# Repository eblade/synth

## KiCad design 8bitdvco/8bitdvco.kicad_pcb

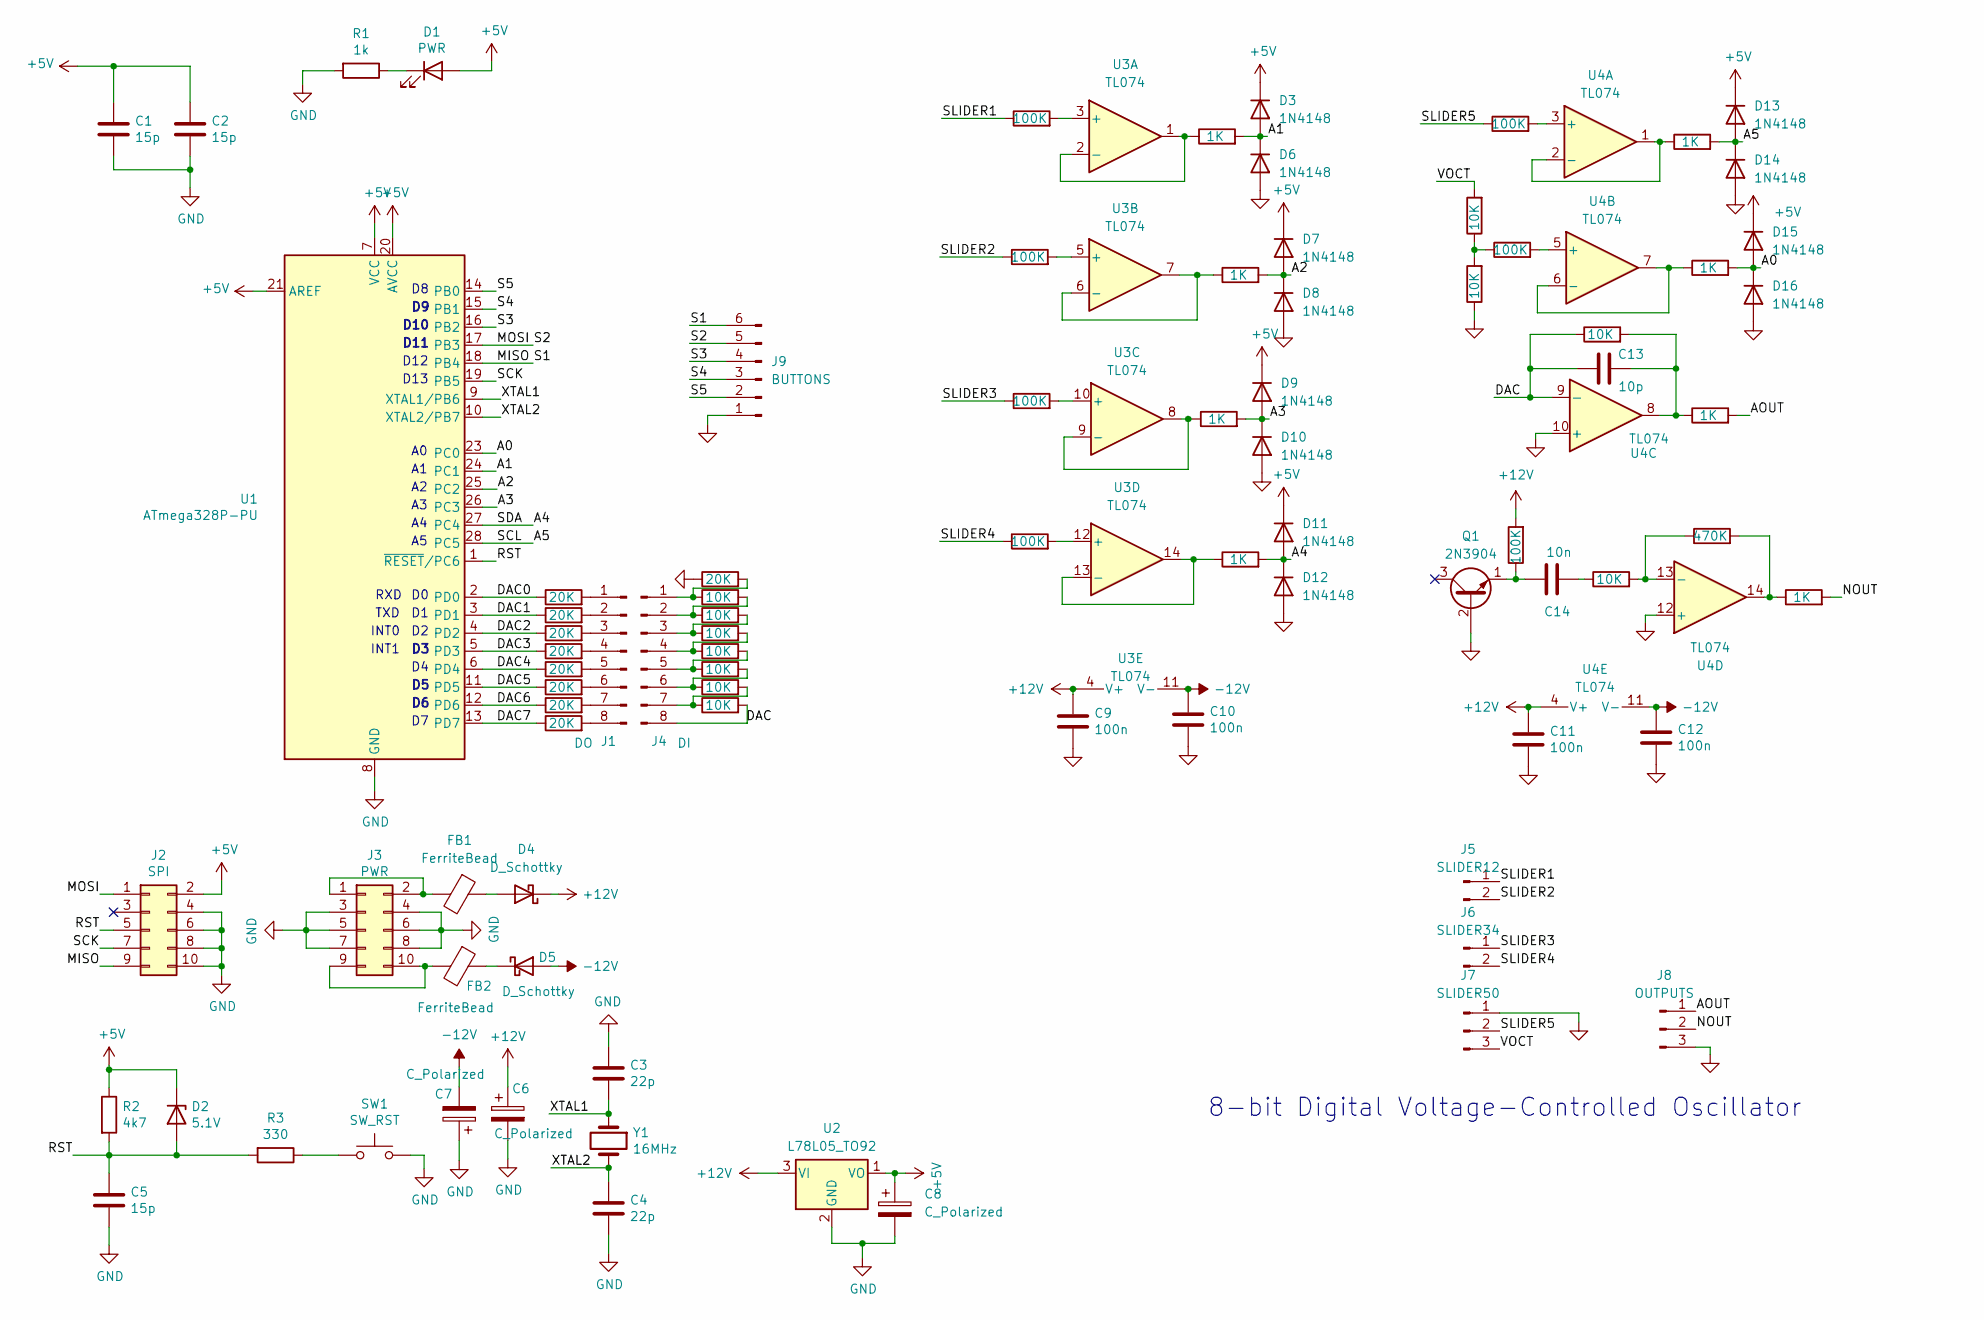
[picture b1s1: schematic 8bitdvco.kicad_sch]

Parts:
C1, C2, C5: 15p; C_Disc_D3.0mm_W1.6mm_P2.50mm
C3, C4: 22p; C_Disc_D3.0mm_W1.6mm_P2.50mm
C6, C7, C8: C_Polarized; CP_Radial_D8.0mm_P2.50mm
C9, C10, C11, C12: 100n; C_Disc_D3.0mm_W1.6mm_P2.50mm
C13: 10p; C_Disc_D3.0mm_W1.6mm_P2.50mm
C14: 10n; C_Disc_D3.0mm_W1.6mm_P2.50mm
D1: PWR; LED_D3.0mm
D2: 5.1V; D_A-405_P7.62mm_Horizontal
D3, D6, D7, D8, D9, D10, D11, D12, D13, D14, D15, D16: 1N4148; D_DO-35_SOD27_P7.62mm_Horizontal
D4, D5: D_Schottky; D_DO-35_SOD27_P7.62mm_Horizontal
FB1, FB2: FerriteBead; R_Axial_DIN0309_L9.0mm_D3.2mm_P12.70mm_Horizontal
J1: DO; PinHeader_1x08_P2.54mm_Vertical
J2: SPI; PinHeader_2x05_P2.54mm_Vertical
J3: PWR; PinHeader_2x05_P2.54mm_Vertical
J4: DI; PinHeader_1x08_P2.54mm_Vertical
J5: SLIDER12; PinHeader_1x02_P2.54mm_Vertical
J6: SLIDER34; PinHeader_1x02_P2.54mm_Vertical
J7: SLIDER50; PinHeader_1x03_P2.54mm_Vertical
J8: OUTPUTS; PinHeader_1x03_P2.54mm_Vertical
J9: BUTTONS; PinHeader_1x06_P2.54mm_Vertical
Q1: 2N3904; TO-92_Inline
R1: 1k; R_Axial_DIN0204_L3.6mm_D1.6mm_P7.62mm_Horizontal
R2: 4k7; R_Axial_DIN0204_L3.6mm_D1.6mm_P7.62mm_Horizontal
R3: 330; R_Axial_DIN0204_L3.6mm_D1.6mm_P7.62mm_Horizontal
R4, R5, R6, R7, R8, R9, R10, R32, R33, R34, R38: 10K; R_Axial_DIN0204_L3.6mm_D1.6mm_P7.62mm_Horizontal
R11, R14, R15, R16, R17, R18, R19, R20, R21: 20K; R_Axial_DIN0204_L3.6mm_D1.6mm_P7.62mm_Horizontal
R12, R23, R24, R25, R28, R29, R35, R36: 1K; R_Axial_DIN0204_L3.6mm_D1.6mm_P7.62mm_Horizontal
R13, R22, R26, R27, R30, R31, R39: 100K; R_Axial_DIN0204_L3.6mm_D1.6mm_P7.62mm_Horizontal
R37: 470K; R_Axial_DIN0204_L3.6mm_D1.6mm_P7.62mm_Horizontal
SW1: SW_RST; SW_PUSH_6mm_H4.3mm
U1: ATmega328P-PU; DIP-28_W7.62mm
U2: L78L05_TO92; TO-92_Inline
U3, U4: TL074; DIP-14_W7.62mm_LongPads
Y1: 16MHz; Crystal_HC18-U_Vertical

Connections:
+5V: C1.2, C2.2, C8.1, D1.2 (A), D2.1 (K), D3.1 (K), D7.1 (K), D9.1 (K), D11.1 (K), D13.1 (K), D15.1 (K), J2.2, R2.1, U1.7 (VCC), U1.20 (AVCC), U1.21 (AREF), U2.1 (VO)
+12V: C6.1, C9.2, C11.2, D4.1 (K), R39.2, U2.3 (VI), U3.4 (V+), U4.4 (V+)
-12V: C7.2, C10.2, C12.2, D5.2 (A), U3.11 (V-), U4.11 (V-)
/A0: D15.2 (A), D16.1 (K), R29.2, U1.23 (PC0)
/A1: D3.2 (A), D6.1 (K), R12.2, U1.24 (PC1)
/A2: D7.2 (A), D8.1 (K), R23.2, U1.25 (PC2)
/A3: D9.2 (A), D10.1 (K), R24.2, U1.26 (PC3)
/A4: D11.2 (A), D12.1 (K), R25.2, U1.27 (PC4)
/A5: D13.2 (A), D14.1 (K), R28.2, U1.28 (PC5)
/AOUT: J8.1, R35.2
/DAC: C13.1, J4.8, R10.2, R34.1, U4.9 (-)
/DAC0: R14.1, U1.2 (PD0)
/DAC1: R15.1, U1.3 (PD1)
/DAC2: R16.1, U1.4 (PD2)
/DAC3: R17.1, U1.5 (PD3)
/DAC4: R18.1, U1.6 (PD4)
/DAC5: R19.1, U1.11 (PD5)
/DAC6: R20.1, U1.12 (PD6)
/DAC7: R21.1, U1.13 (PD7)
/MISO: J2.9, J9.6, U1.18 (PB4)
/MOSI: J2.1, J9.5, U1.17 (PB3)
/NOUT: J8.2, R36.2
/RST: C5.2, D2.2 (A), J2.5, R2.2, R3.2, U1.1 (~RESET/PC6)
/S3: J9.4, U1.16 (PB2)
/S4: J9.3, U1.15 (PB1)
/S5: J9.2, U1.14 (PB0)
/SCK: J2.7, U1.19 (PB5)
/SLIDER1: J5.1, R13.1
/SLIDER2: J5.2, R22.1
/SLIDER3: J6.1, R26.1
/SLIDER4: J6.2, R27.1
/SLIDER5: J7.2, R30.1
/VOCT: J7.3, R32.2
/XTAL1: C3.2, U1.9 (XTAL1/PB6), Y1.1
/XTAL2: C4.1, U1.10 (XTAL2/PB7), Y1.2
GND: C1.1, C2.1, C3.1, C4.2, C5.1, C6.2, C7.1, C8.2, C9.1, C10.1, C11.1, C12.1, D6.2 (A), D8.2 (A), D10.2 (A), D12.2 (A), D14.2 (A), D16.2 (A), J2.4, J2.6, J2.8, J2.10, J3.3, J3.4, J3.5, J3.6, J3.7, J3.8, J7.1, J8.3, J9.1, Q1.2 (B), R1.2, R11.1, R33.1, SW1.2, U1.8 (GND), U1.22 (GND), U2.2 (GND), U4.10 (+), U4.12 (+)
unnamed: C13.2, R34.2, R35.1, U4.8
unnamed: C14.1, R38.1
unnamed: D1.1 (K), R1.1
unnamed: D4.2 (A), FB1.1
unnamed: D5.1 (K), FB2.1
unnamed: J1.1, R14.2
unnamed: J1.2, R15.2
unnamed: J1.3, R16.2
unnamed: J1.4, R17.2
unnamed: J1.5, R18.2
unnamed: J1.6, R19.2
unnamed: J1.7, R20.2
unnamed: J1.8, R21.2
unnamed: FB1.2, J3.1, J3.2
unnamed: FB2.2, J3.9, J3.10
unnamed: J4.1, R4.1, R11.2
unnamed: J4.2, R4.2, R5.1
unnamed: J4.3, R5.2, R6.1
unnamed: J4.4, R6.2, R7.1
unnamed: J4.5, R7.2, R8.1
unnamed: J4.6, R8.2, R9.1
unnamed: J4.7, R9.2, R10.1
unnamed: C14.2, Q1.1 (E), R39.1
unnamed: R3.1, SW1.1
unnamed: R31.1, R32.1, R33.2
unnamed: R36.1, R37.2, U4.14
unnamed: R13.2, U3.3 (+)
unnamed: R12.1, U3.1, U3.2 (-)
unnamed: R22.2, U3.5 (+)
unnamed: R23.1, U3.6 (-), U3.7
unnamed: R26.2, U3.10 (+)
unnamed: R24.1, U3.8, U3.9 (-)
unnamed: R27.2, U3.12 (+)
unnamed: R25.1, U3.13 (-), U3.14
unnamed: R30.2, U4.3 (+)
unnamed: R28.1, U4.1, U4.2 (-)
unnamed: R31.2, U4.5 (+)
unnamed: R29.1, U4.6 (-), U4.7
unnamed: R37.1, R38.2, U4.13 (-)

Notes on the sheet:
D12
D10
RXD
D13
D11
INT1
TXD
8-bit Digital Voltage-Controlled Oscillator
INT0

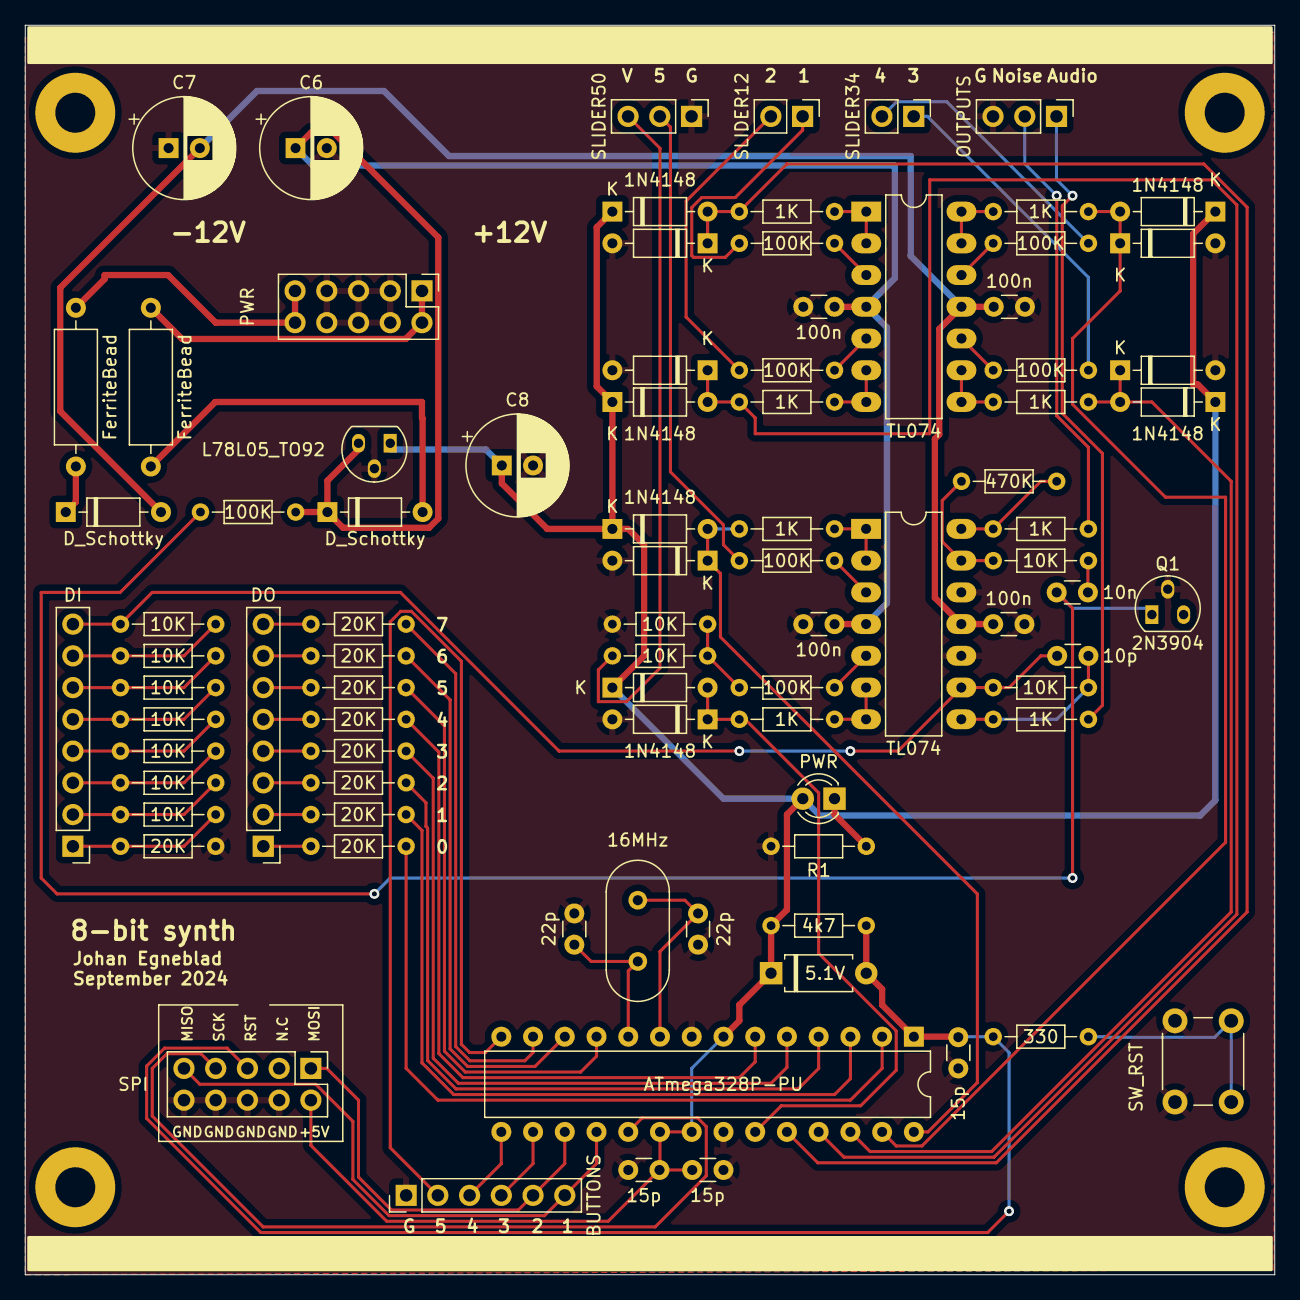
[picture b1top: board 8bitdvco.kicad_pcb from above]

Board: 2 copper layers, 100.0 x 100.0 mm, 87 parts (0 on the bottom side), 75 nets.

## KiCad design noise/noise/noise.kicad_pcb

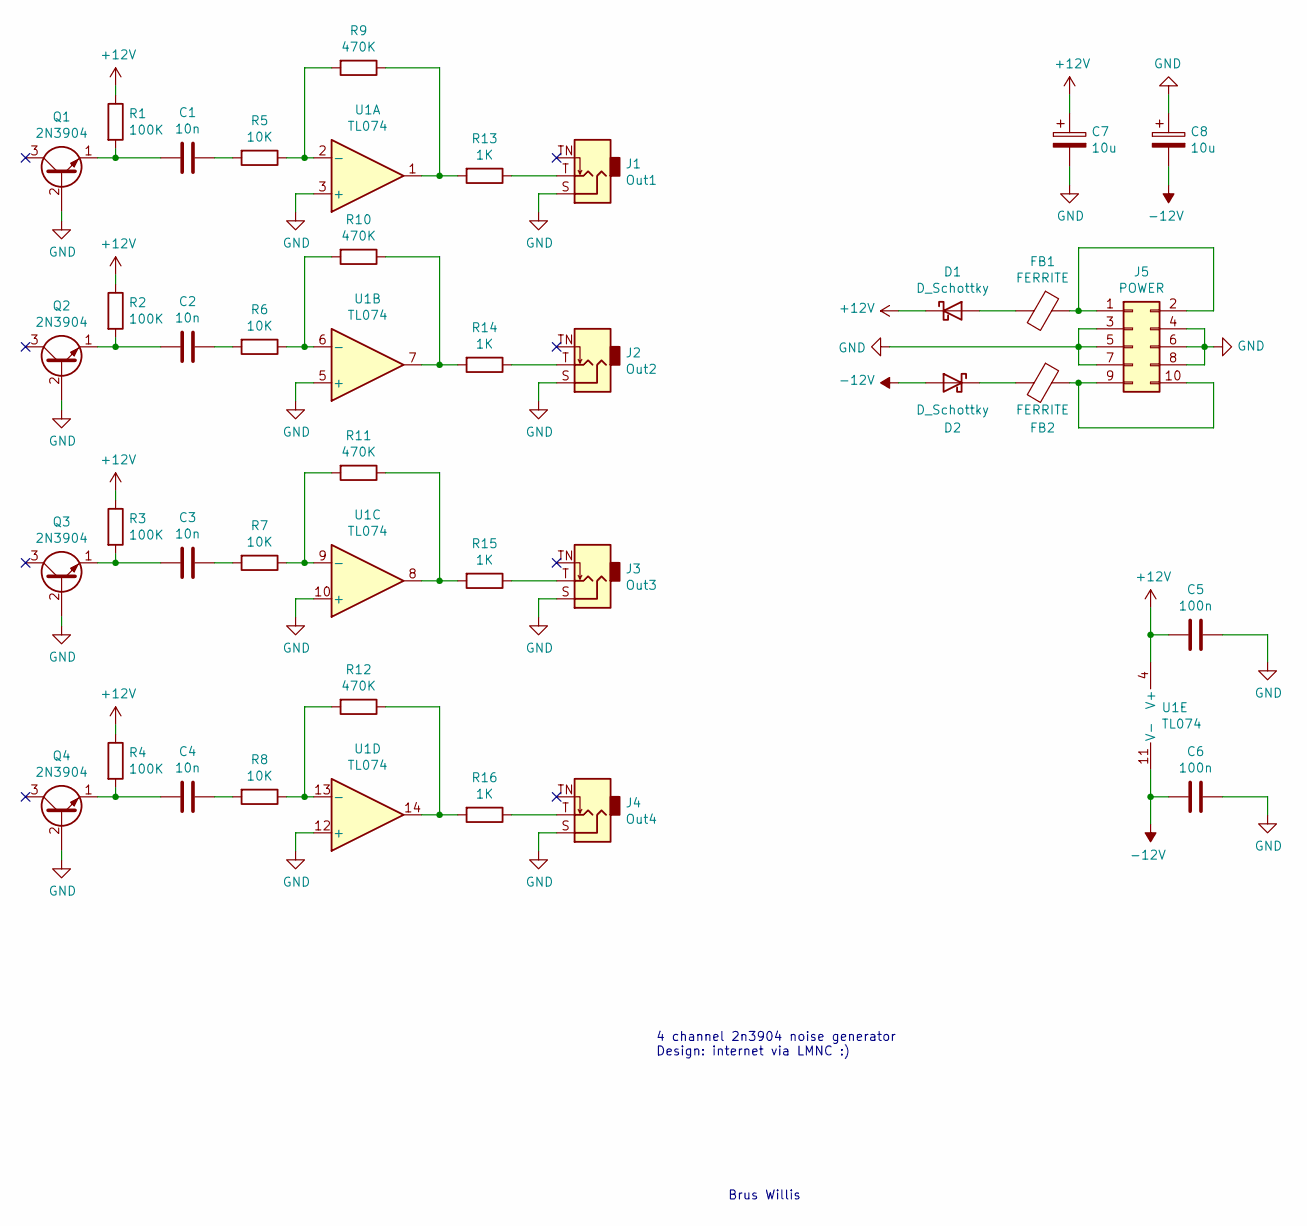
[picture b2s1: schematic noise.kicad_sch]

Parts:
C1, C2, C3, C4: 10n; C_Disc_D4.3mm_W1.9mm_P5.00mm
C5, C6: 100n; C_Disc_D4.3mm_W1.9mm_P5.00mm
C7, C8: 10u; CP_Radial_D5.0mm_P2.00mm
D1, D2: D_Schottky; D_5W_P12.70mm_Horizontal
FB1, FB2: FERRITE; R_Axial_DIN0411_L9.9mm_D3.6mm_P12.70mm_Horizontal
J1: Out1; Jack_3.5mm_QingPu_WQP-PJ398SM_Vertical_CircularHoles
J2: Out2; Jack_3.5mm_QingPu_WQP-PJ398SM_Vertical_CircularHoles
J3: Out3; Jack_3.5mm_QingPu_WQP-PJ398SM_Vertical_CircularHoles
J4: Out4; Jack_3.5mm_QingPu_WQP-PJ398SM_Vertical_CircularHoles
J5: POWER; PinHeader_2x05_P2.54mm_Vertical
Q1, Q2, Q3, Q4: 2N3904; TO-92_Inline
R1, R2, R3, R4: 100K; R_Axial_DIN0204_L3.6mm_D1.6mm_P7.62mm_Horizontal
R5, R6, R7, R8: 10K; R_Axial_DIN0204_L3.6mm_D1.6mm_P7.62mm_Horizontal
R9, R10, R11, R12: 470K; R_Axial_DIN0204_L3.6mm_D1.6mm_P7.62mm_Horizontal
R13, R14, R15, R16: 1K; R_Axial_DIN0204_L3.6mm_D1.6mm_P7.62mm_Horizontal
U1: TL074; DIP-14_W7.62mm_Socket

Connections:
+12V: C5.2, C7.1, D1.1 (K), R1.1, R2.1, R3.1, R4.1, U1.4 (V+)
-12V: C6.2, C8.2, D2.2 (A), U1.11 (V-)
GND: C5.1, C6.1, C7.2, C8.1, J1.S, J2.S, J3.S, J4.S, J5.3, J5.4, J5.5, J5.6, J5.7, J5.8, Q1.2 (B), Q2.2 (B), Q3.2 (B), Q4.2 (B), U1.3 (+), U1.5 (+), U1.10 (+), U1.12 (+)
unnamed: C1.1, R5.2
unnamed: C1.2, Q1.1 (E), R1.2
unnamed: C2.1, R6.2
unnamed: C2.2, Q2.1 (E), R2.2
unnamed: C3.1, R7.2
unnamed: C3.2, Q3.1 (E), R3.2
unnamed: C4.1, R8.2
unnamed: C4.2, Q4.1 (E), R4.2
unnamed: D1.2 (A), FB1.2
unnamed: D2.1 (K), FB2.2
unnamed: FB1.1, J5.1, J5.2
unnamed: FB2.1, J5.9, J5.10
unnamed: J1.T, R13.1
unnamed: J2.T, R14.1
unnamed: J3.T, R15.1
unnamed: J4.T, R16.1
unnamed: R5.1, R9.2, U1.2 (-)
unnamed: R10.1, R14.2, U1.7
unnamed: R6.1, R10.2, U1.6 (-)
unnamed: R11.1, R15.2, U1.8
unnamed: R7.1, R11.2, U1.9 (-)
unnamed: R12.1, R16.2, U1.14
unnamed: R8.1, R12.2, U1.13 (-)
unnamed: R9.1, R13.2, U1.1

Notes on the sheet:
Brus Willis
4 channel 2n3904 noise generator Design: internet via LMNC :)

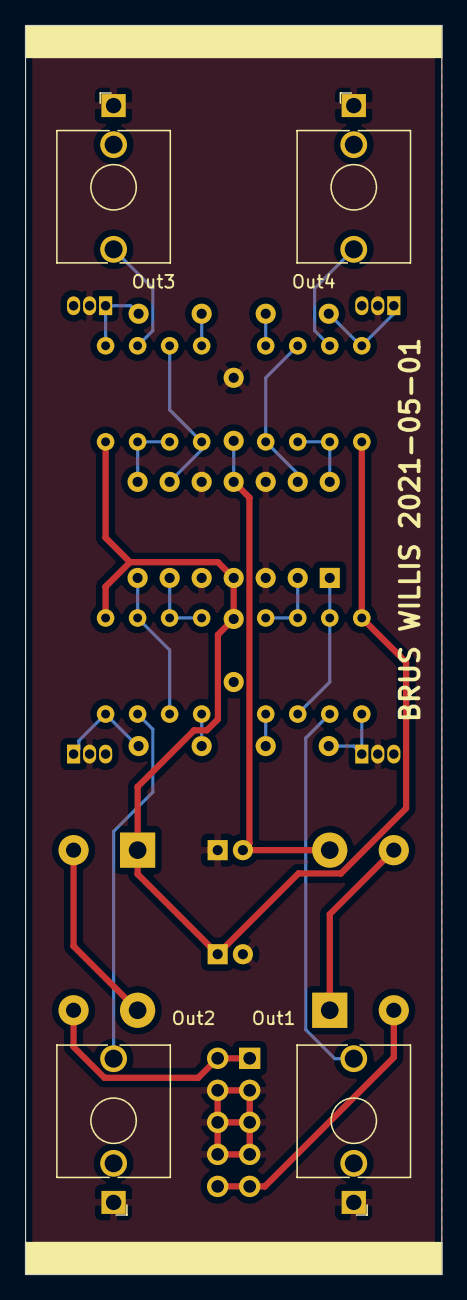
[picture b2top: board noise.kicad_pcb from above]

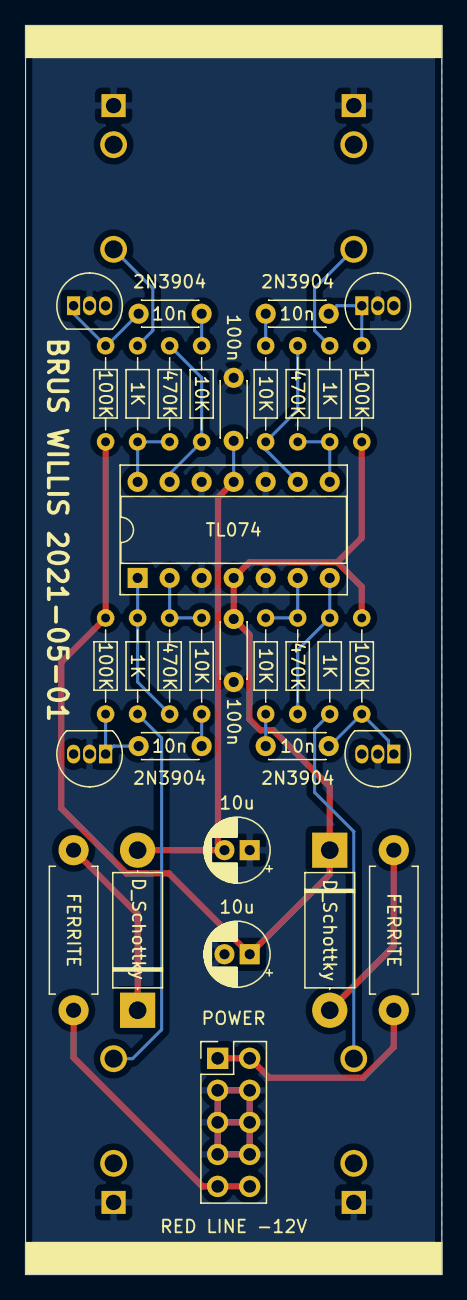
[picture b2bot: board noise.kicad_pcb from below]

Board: 2 copper layers, 33.0 x 99.1 mm, 38 parts (34 on the bottom side), 27 nets.

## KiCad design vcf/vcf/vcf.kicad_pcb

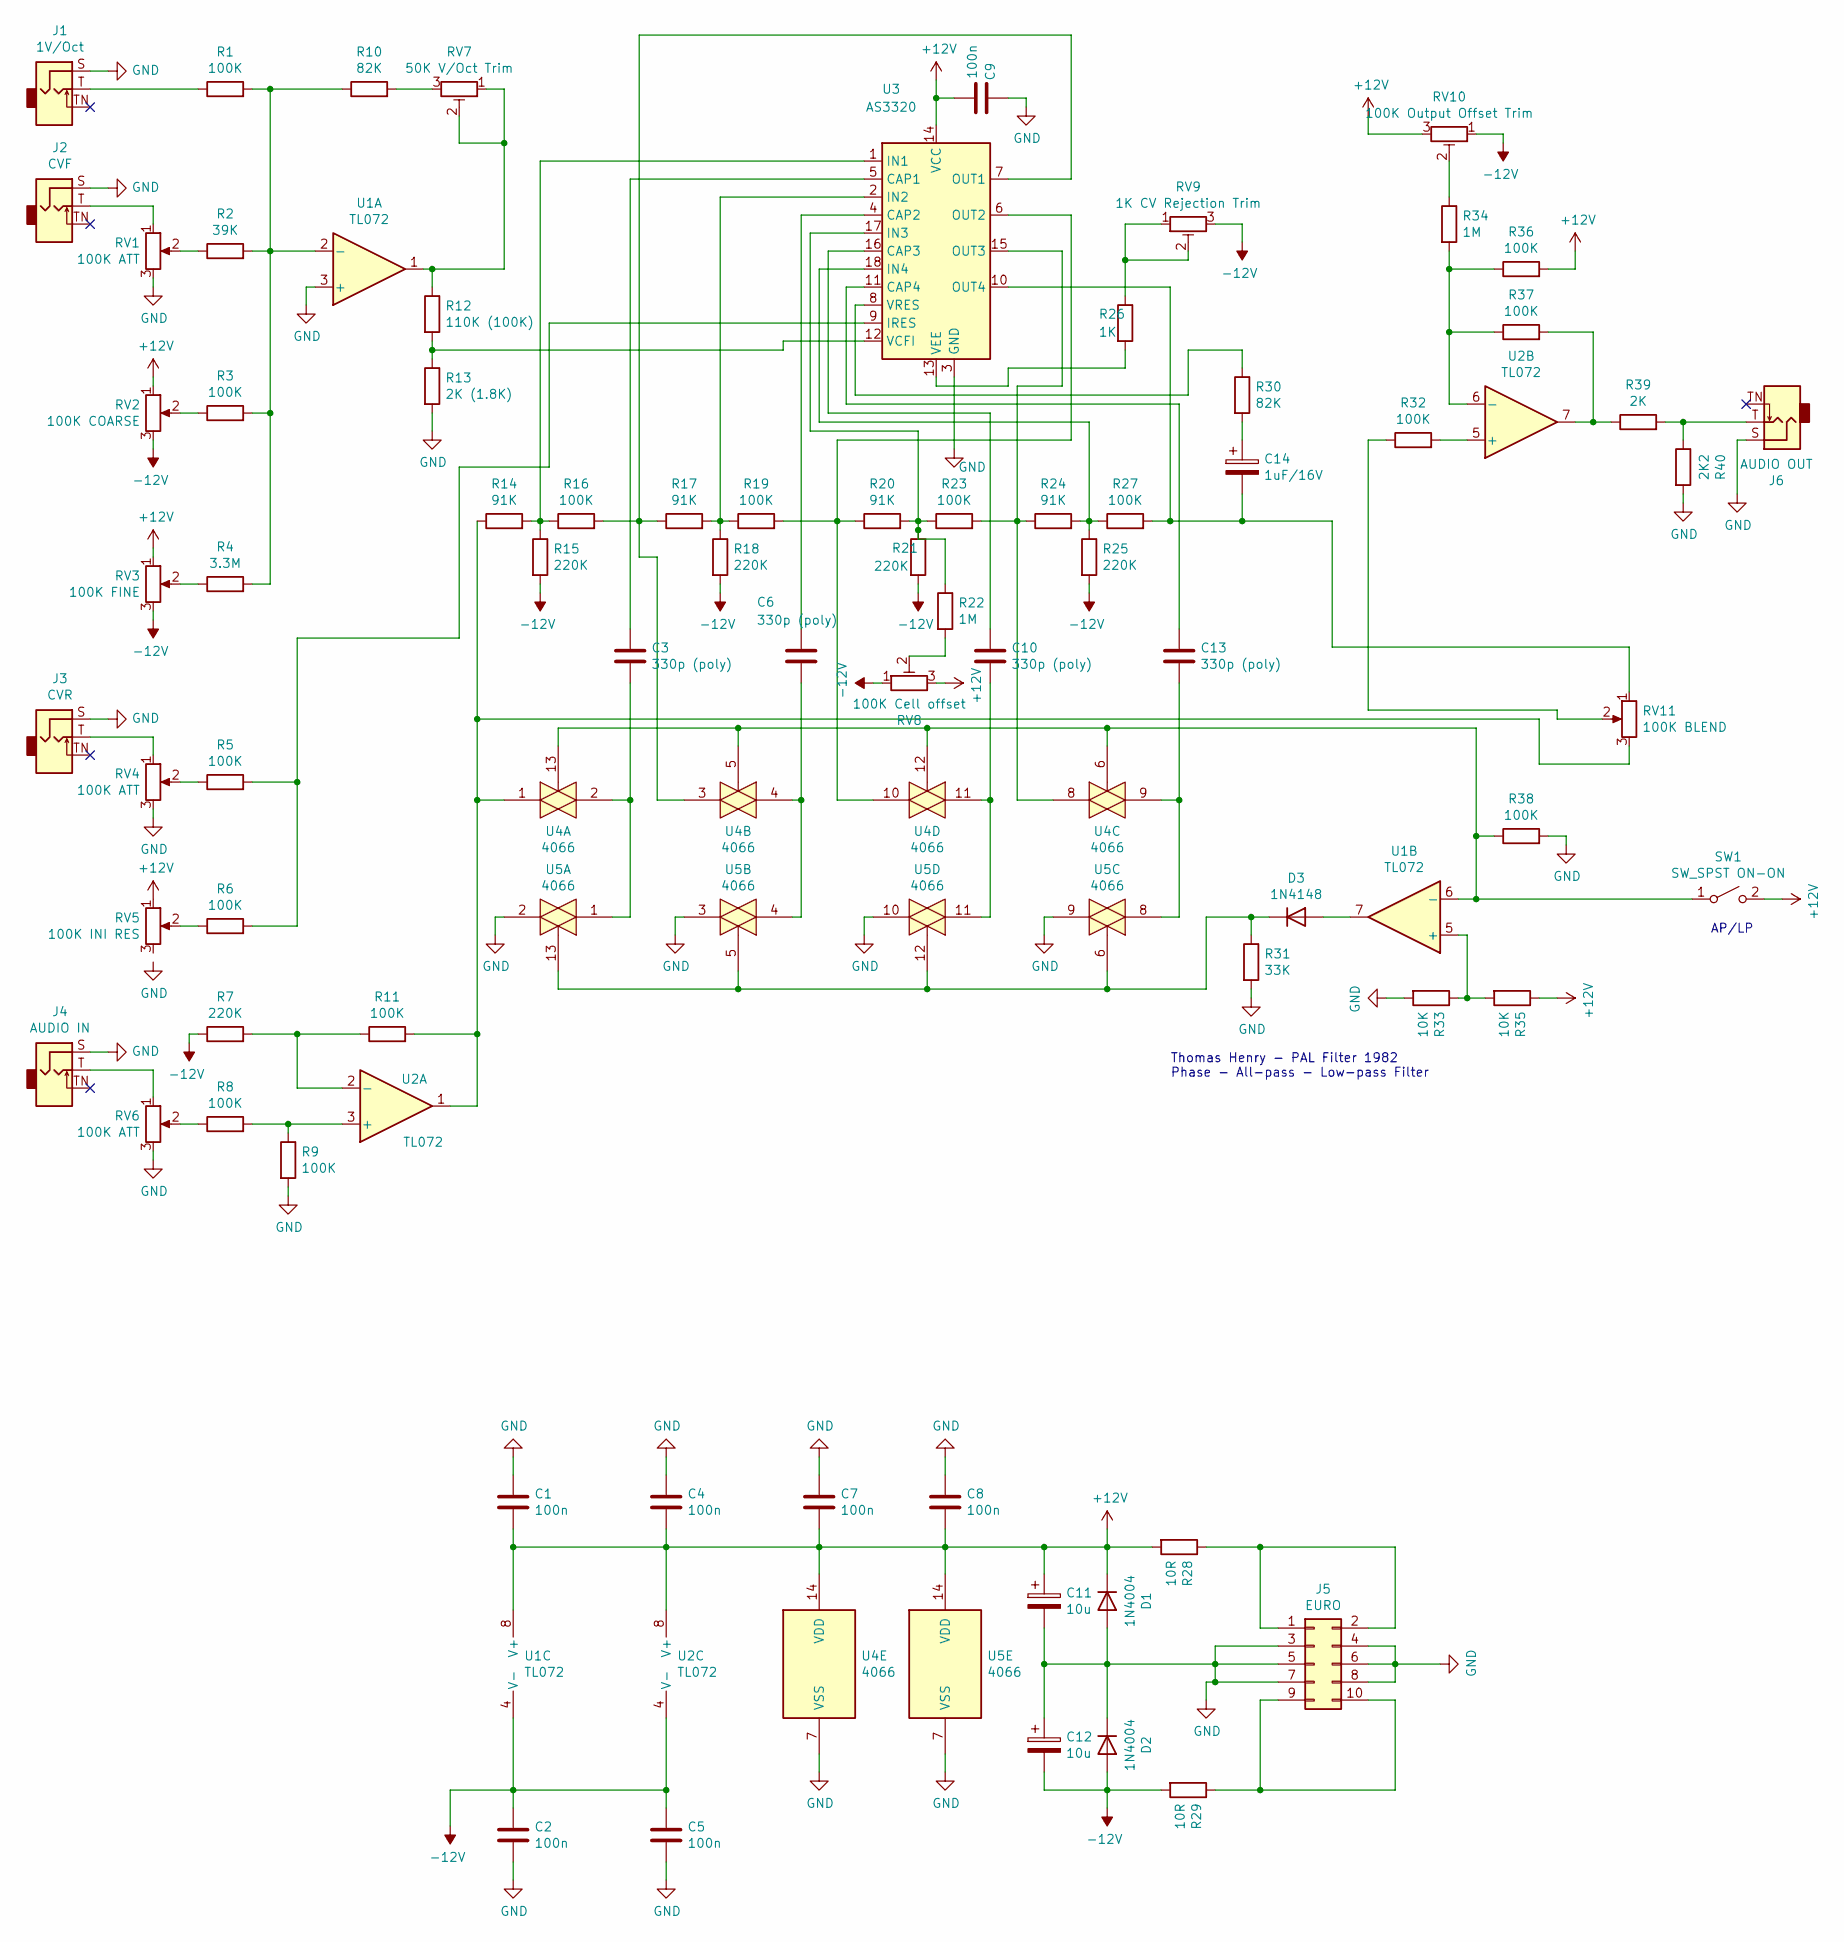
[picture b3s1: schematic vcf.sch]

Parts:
C1, C2, C4, C5, C7, C8, C9: 100n; C_Disc_D3.0mm_W1.6mm_P2.50mm
C3, C6, C10, C13: 330p (poly); C_Disc_D6.0mm_W2.5mm_P5.00mm
C11, C12: 10u; CP_Radial_Tantal_D5.0mm_P2.50mm
C14: 1uF/16V; CP_Radial_Tantal_D5.0mm_P2.50mm
D1, D2: 1N4004; D_DO-35_SOD27_P7.62mm_Horizontal
D3: 1N4148; D_DO-35_SOD27_P7.62mm_Horizontal
J1: 1V/Oct; Jack_3.5mm_QingPu_WQP-PJ398SM_Vertical_CircularHoles
J2: CVF; Jack_3.5mm_QingPu_WQP-PJ398SM_Vertical_CircularHoles
J3: CVR; Jack_3.5mm_QingPu_WQP-PJ398SM_Vertical_CircularHoles
J4: AUDIO IN; Jack_3.5mm_QingPu_WQP-PJ398SM_Vertical_CircularHoles
J5: EURO; PinHeader_2x05_P2.54mm_Vertical
J6: AUDIO OUT; Jack_3.5mm_QingPu_WQP-PJ398SM_Vertical_CircularHoles
R1, R3, R5, R6, R8, R9, R11, R16, R19, R23, R27, R32, R36, R37, R38: 100K; R_Axial_DIN0204_L3.6mm_D1.6mm_P7.62mm_Horizontal
R2: 39K; R_Axial_DIN0204_L3.6mm_D1.6mm_P7.62mm_Horizontal
R4: 3.3M; R_Axial_DIN0204_L3.6mm_D1.6mm_P7.62mm_Horizontal
R7, R15, R18, R21, R25: 220K; R_Axial_DIN0204_L3.6mm_D1.6mm_P7.62mm_Horizontal
R10, R30: 82K; R_Axial_DIN0204_L3.6mm_D1.6mm_P7.62mm_Horizontal
R12: 110K (100K); R_Axial_DIN0204_L3.6mm_D1.6mm_P7.62mm_Horizontal
R13: 2K (1.8K); R_Axial_DIN0204_L3.6mm_D1.6mm_P7.62mm_Horizontal
R14, R17, R20, R24: 91K; R_Axial_DIN0204_L3.6mm_D1.6mm_P7.62mm_Horizontal
R22, R34: 1M; R_Axial_DIN0204_L3.6mm_D1.6mm_P7.62mm_Horizontal
R26: 1K; R_Axial_DIN0204_L3.6mm_D1.6mm_P7.62mm_Horizontal
R28, R29: 10R; R_Axial_DIN0204_L3.6mm_D1.6mm_P7.62mm_Horizontal
R31: 33K; R_Axial_DIN0204_L3.6mm_D1.6mm_P7.62mm_Horizontal
R33, R35: 10K; R_Axial_DIN0204_L3.6mm_D1.6mm_P7.62mm_Horizontal
R39: 2K; R_Axial_DIN0204_L3.6mm_D1.6mm_P7.62mm_Horizontal
R40: 2K2; R_Axial_DIN0204_L3.6mm_D1.6mm_P7.62mm_Horizontal
RV1, RV4, RV6: 100K ATT; Potentiometer_Alps_RK09L_Single_Vertical
RV2: 100K COARSE; Potentiometer_Alps_RK09L_Single_Vertical
RV3: 100K FINE; Potentiometer_Alps_RK09L_Single_Vertical
RV5: 100K INI RES; Potentiometer_Alps_RK09L_Single_Vertical
RV7: 50K V/Oct Trim; Potentiometer_Bourns_3296W_Vertical
RV8: 100K Cell offset; Potentiometer_Bourns_3296W_Vertical
RV9: 1K CV Rejection Trim; Potentiometer_Bourns_3296W_Vertical
RV10: 100K Output Offset Trim; Potentiometer_Bourns_3296W_Vertical
RV11: 100K BLEND; Potentiometer_Alps_RK09L_Single_Vertical
SW1: SW_SPST ON-ON; SW_Toggle_Blue_wSlots
U1, U2: TL072; DIP-8_W7.62mm_Socket
U3: AS3320; DIP-18_W7.62mm
U4, U5: 4066; DIP-14_W7.62mm_Socket

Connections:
+12V: C1.2, C4.2, C7.2, C8.2, C9.2, C11.1, D1.1 (K), R28.2, R35.1, R36.2, RV2.1, RV3.1, RV5.1, RV8.3, RV10.3, SW1.2 (B), U1.8 (V+), U2.8 (V+), U3.14 (VCC), U4.14 (VDD), U5.14 (VDD)
-12V: C2.1, C5.1, C12.2, D2.2 (A), R7.1, R15.2, R18.2, R21.2, R25.2, R29.2, RV2.3, RV3.3, RV8.1, RV9.3, RV10.1, U1.4 (V-), U2.4 (V-)
GND: C1.1, C2.2, C4.1, C5.2, C7.1, C8.1, C9.1, C11.2, C12.1, D1.2 (A), D2.1 (K), J1.S, J2.S, J3.S, J4.S, J5.3, J5.4, J5.5, J5.6, J5.7, J5.8, J6.S, R9.2, R13.2, R31.2, R33.2, R38.2, R40.2, RV1.3, RV4.3, RV6.3, U1.3 (+), U3.3 (GND), U4.7 (VSS), U5.2, U5.3, U5.7 (VSS), U5.9, U5.10
unnamed: C3.1, U3.5 (CAP1)
unnamed: C3.2, U4.2, U5.1
unnamed: C6.1, U3.4 (CAP2)
unnamed: C6.2, U4.4, U5.4
unnamed: C10.1, U3.16 (CAP3)
unnamed: C10.2, U4.11, U5.11
unnamed: C13.1, U3.11 (CAP4)
unnamed: C13.2, U4.9, U5.8
unnamed: C14.1, R30.2
unnamed: C14.2, R27.2, RV11.1, U3.10 (OUT4)
unnamed: D3.1 (K), R31.1, U5.5, U5.6, U5.12, U5.13
unnamed: D3.2 (A), U1.7
unnamed: J1.T, R1.1
unnamed: J2.T, RV1.1
unnamed: J3.T, RV4.1
unnamed: J4.T, RV6.1
unnamed: J5.1, J5.2, R28.1
unnamed: J5.9, J5.10, R29.1
unnamed: J6.T, R39.2, R40.1
unnamed: R1.2, R2.2, R3.2, R4.2, R10.1, U1.2 (-)
unnamed: R2.1, RV1.2
unnamed: R3.1, RV2.2
unnamed: R4.1, RV3.2
unnamed: R5.1, RV4.2
unnamed: R5.2, R6.2, U3.9 (IRES)
unnamed: R6.1, RV5.2
unnamed: R8.1, RV6.2
unnamed: R8.2, R9.1, U2.3 (+)
unnamed: R10.2, RV7.3
unnamed: R7.2, R11.1, U2.2 (-)
unnamed: R11.2, R14.1, RV11.3, U2.1, U4.1
unnamed: R12.1, RV7.1, RV7.2, U1.1
unnamed: R12.2, R13.1, U3.12 (VCFI)
unnamed: R14.2, R15.1, R16.1, U3.1 (IN1)
unnamed: R16.2, R17.1, U3.7 (OUT1), U4.3
unnamed: R17.2, R18.1, R19.1, U3.2 (IN2)
unnamed: R19.2, R20.1, U3.6 (OUT2), U4.10
unnamed: R20.2, R21.1, R22.1, R23.1, U3.17 (IN3)
unnamed: R22.2, RV8.2
unnamed: R23.2, R24.1, U3.15 (OUT3), U4.8
unnamed: R24.2, R25.1, R27.1, U3.18 (IN4)
unnamed: R26.1, RV9.1, RV9.2
unnamed: R26.2, U3.13 (VEE)
unnamed: R30.1, U3.8 (VRES)
unnamed: R32.1, RV11.2
unnamed: R32.2, U2.5 (+)
unnamed: R33.1, R35.2, U1.5 (+)
unnamed: R34.1, RV10.2
unnamed: R34.2, R36.1, R37.1, U2.6 (-)
unnamed: R37.2, R39.1, U2.7
unnamed: R38.1, SW1.1 (A), U1.6 (-), U4.5, U4.6, U4.12, U4.13

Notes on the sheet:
Thomas Henry - PAL Filter 1982 Phase - All-pass - Low-pass Filter
AP/LP

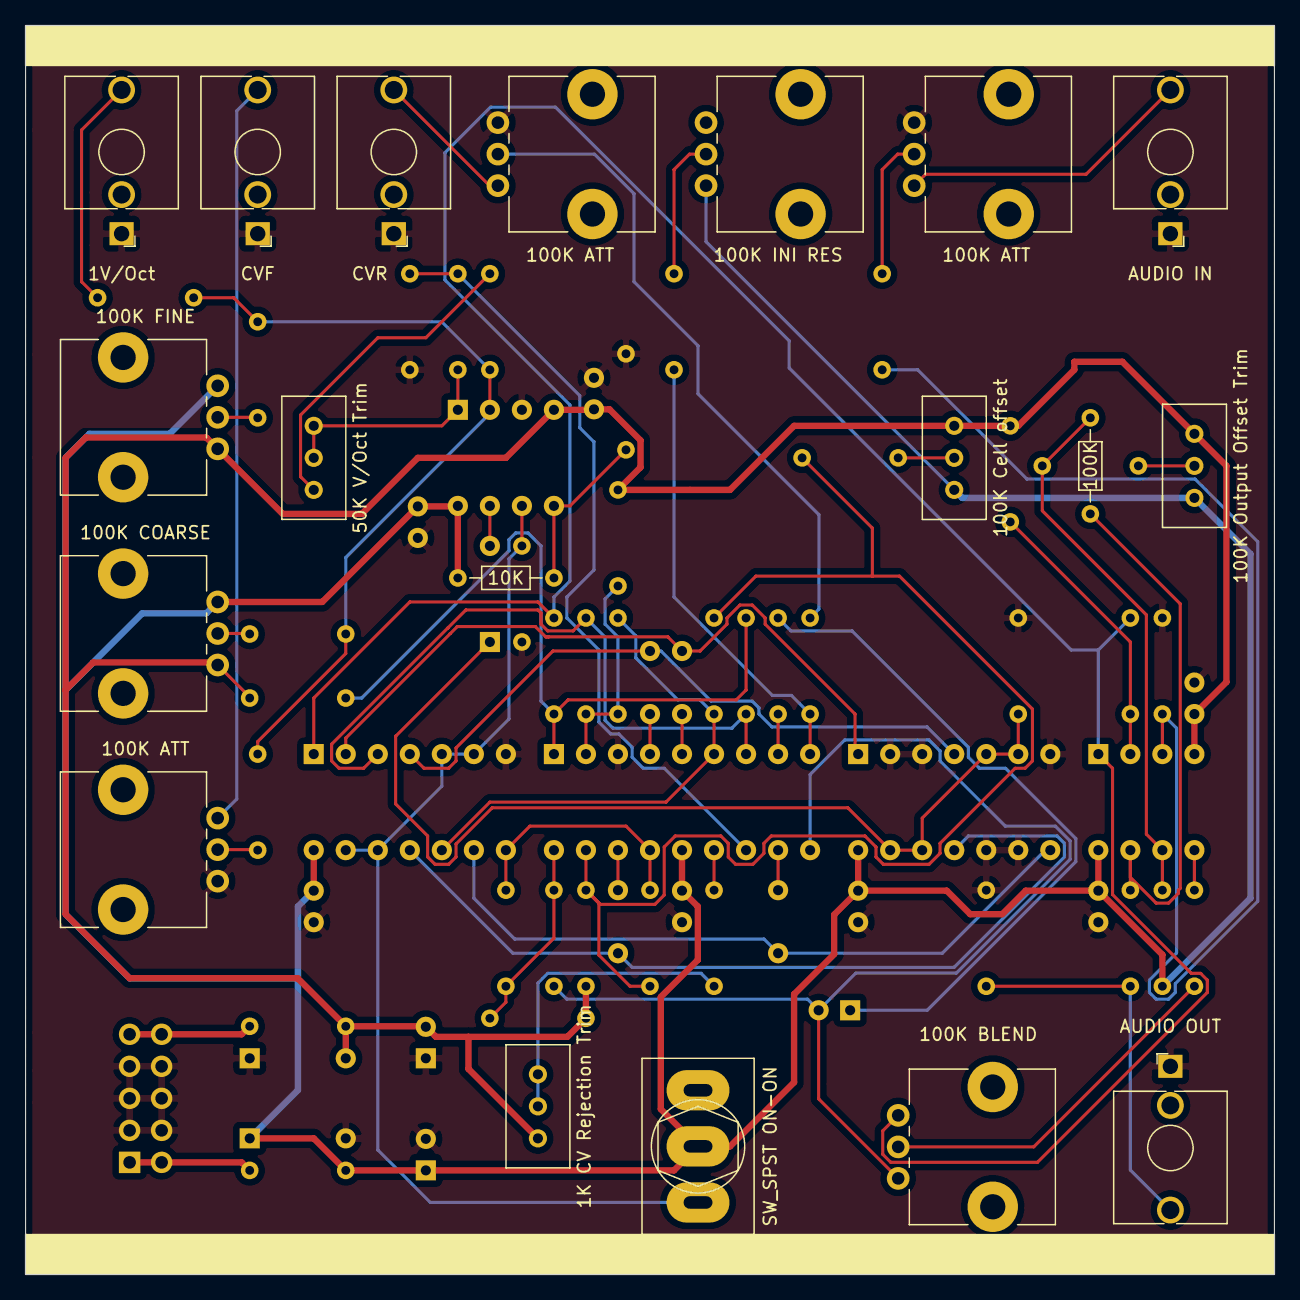
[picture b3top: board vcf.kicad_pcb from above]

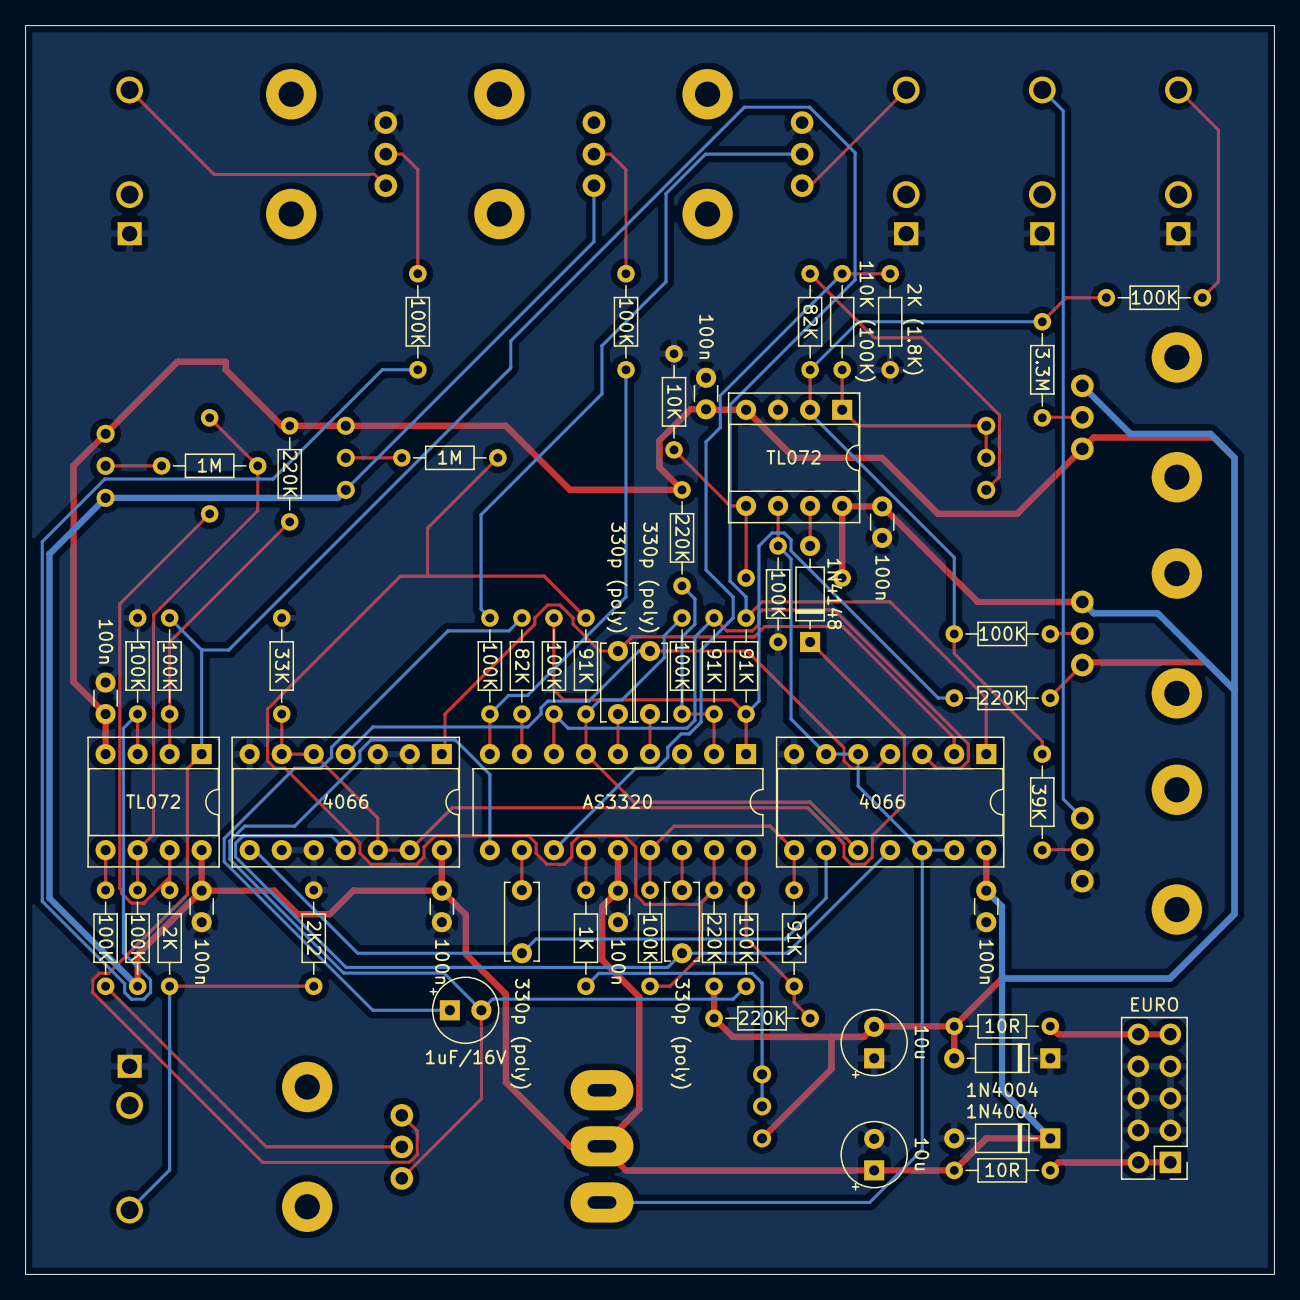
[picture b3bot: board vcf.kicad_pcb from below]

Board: 2 copper layers, 99.1 x 99.1 mm, 80 parts (61 on the bottom side), 54 nets.
